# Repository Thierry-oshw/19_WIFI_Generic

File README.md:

# 19_WIFI_Generic
 WIFI board for generic purposes

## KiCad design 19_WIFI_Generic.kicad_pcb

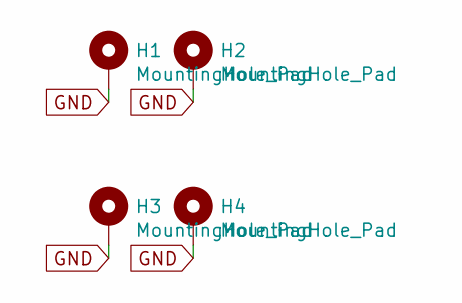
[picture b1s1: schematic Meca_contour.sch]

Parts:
H1, H2, H3, H4: MountingHole_Pad; MountingHole_3.2mm_M3_Pad_Via

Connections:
GND: H1.1, H2.1, H3.1, H4.1; also elsewhere on the board

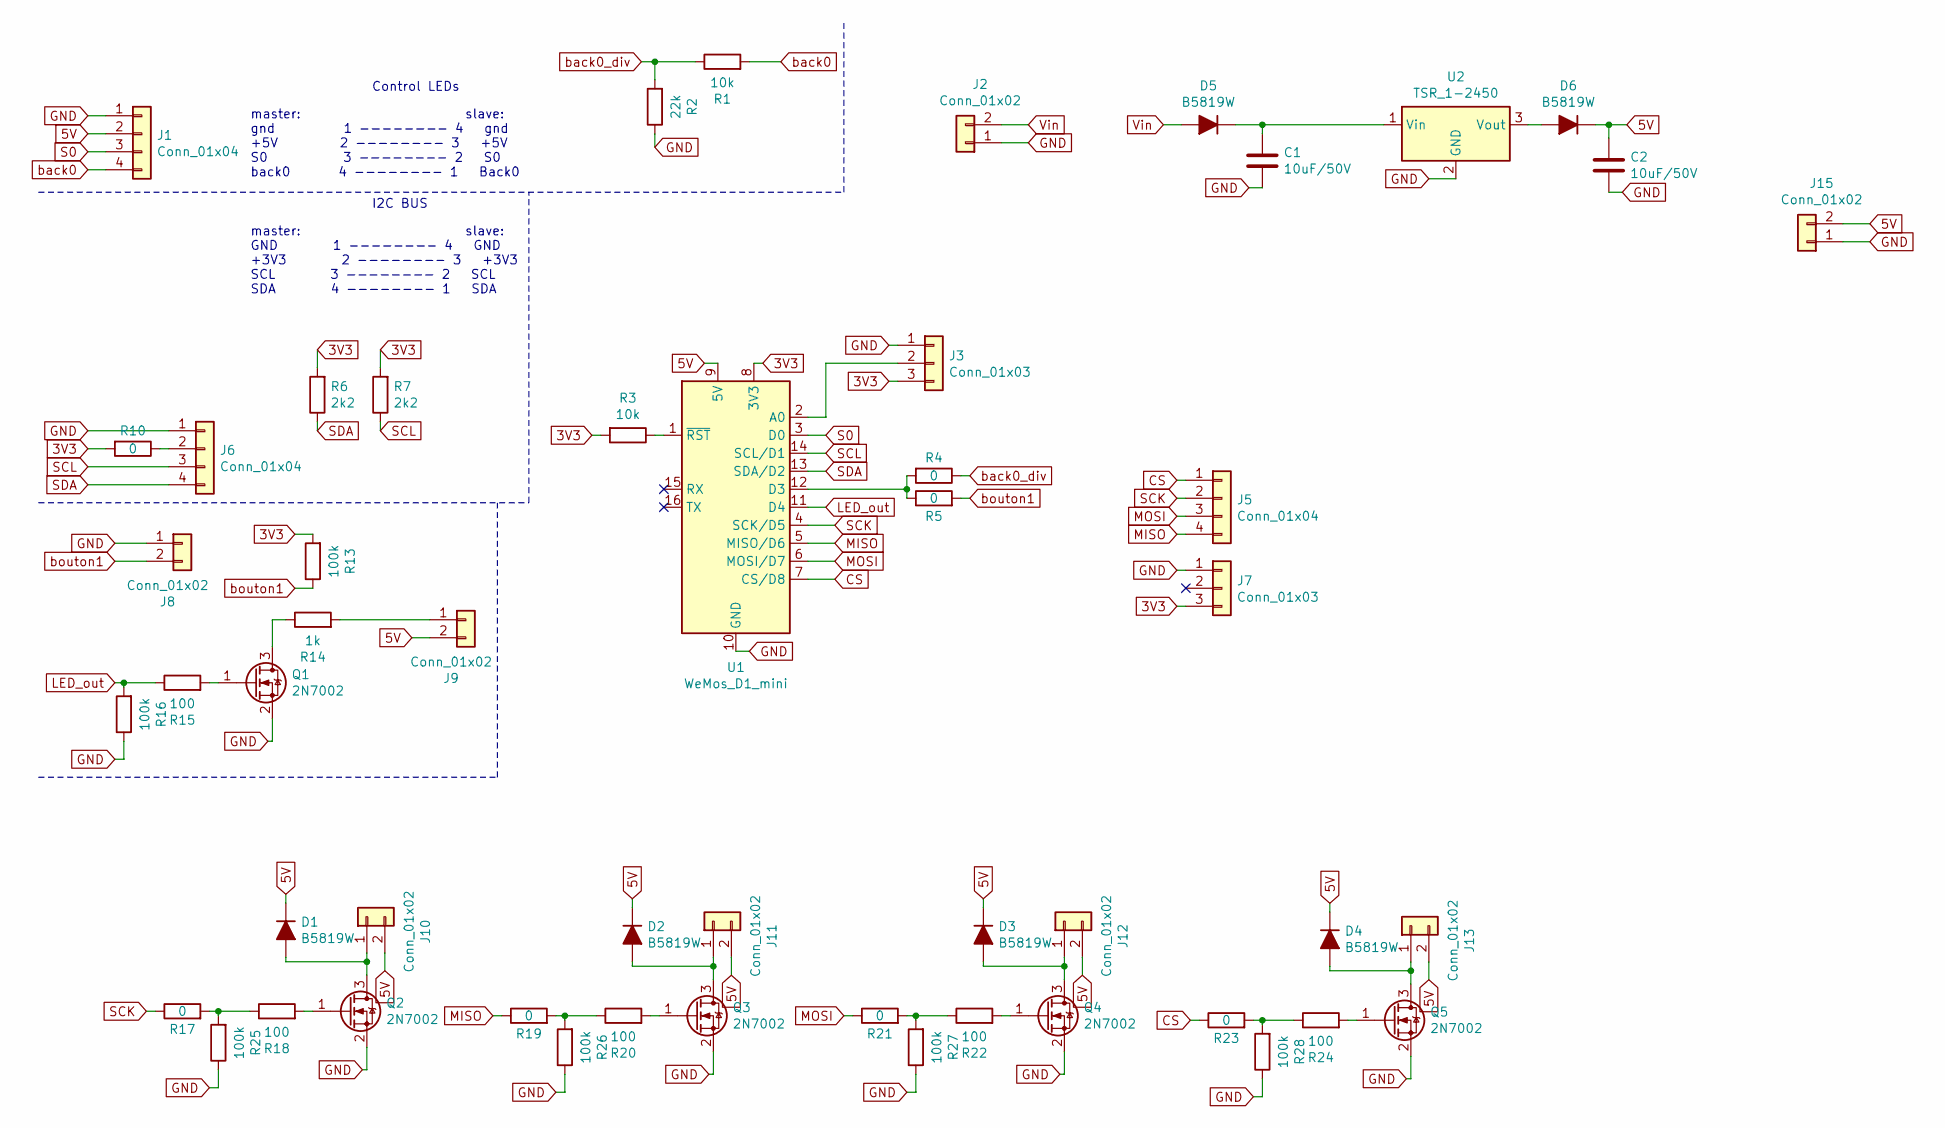
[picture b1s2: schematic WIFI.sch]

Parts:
C1, C2: 10uF/50V; C_1210_3225Metric
D1, D2, D3, D4, D5, D6: B5819W; D_SOD-123
J1, J5, J6: Conn_01x04; JST_XH_B4B-XH-A_1x04_P2.50mm_Vertical
J2, J8, J9, J10, J11, J12, J13, J15: Conn_01x02; JST_XH_B2B-XH-A_1x02_P2.50mm_Vertical
J3, J7: Conn_01x03; JST_XH_B3B-XH-A_1x03_P2.50mm_Vertical
Q1, Q2, Q3, Q4, Q5: 2N7002; SOT-23
R1, R3: 10k; R_0603_1608Metric_Pad1.05x0.95mm_HandSolder
R2: 22k; R_0603_1608Metric_Pad1.05x0.95mm_HandSolder
R4, R5, R10, R17, R19, R21, R23: 0; R_0603_1608Metric_Pad1.05x0.95mm_HandSolder
R6, R7: 2k2; R_0603_1608Metric_Pad1.05x0.95mm_HandSolder
R13, R16, R25, R26, R27, R28: 100k; R_0603_1608Metric_Pad1.05x0.95mm_HandSolder
R14: 1k; R_0603_1608Metric_Pad1.05x0.95mm_HandSolder
R15, R18, R20, R22, R24: 100; R_0603_1608Metric_Pad1.05x0.95mm_HandSolder
U1: WeMos_D1_mini; WEMOS_D1_mini_light
U2: TSR_1-2450; Converter_DCDC_TRACO_TSR-1_THT

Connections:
3V3: J3.3, J7.3, R3.2, R6.2, R7.2, R10.2, R13.2, U1.8 (3V3)
5V: C2.1, D1.1 (K), D2.1 (K), D3.1 (K), D4.1 (K), D6.1 (K), J1.2, J9.2, J10.2, J11.2, J12.2, J13.2, J15.2, U1.9 (5V)
CS: J5.1, R23.1, U1.7 (CS/D8)
GND: C1.2, C2.2, J1.1, J2.1, J3.1, J6.1, J7.1, J8.1, J15.1, Q1.2 (S), Q2.2 (S), Q3.2 (S), Q4.2 (S), Q5.2 (S), R2.1, R16.1, R25.1, R26.1, R27.1, R28.1, U1.10 (GND), U2.2 (GND); also elsewhere on the board
LED_out: R15.1, R16.2, U1.11 (D4)
MISO: J5.4, R19.1, U1.5 (MISO/D6)
MOSI: J5.3, R21.1, U1.6 (MOSI/D7)
unnamed: C1.1, D5.1 (K), U2.1 (Vin)
unnamed: D1.2 (A), J10.1, Q2.3 (D)
unnamed: D2.2 (A), J11.1, Q3.3 (D)
unnamed: D3.2 (A), J12.1, Q4.3 (D)
unnamed: D4.2 (A), J13.1, Q5.3 (D)
unnamed: D6.2 (A), U2.3 (Vout)
unnamed: J3.2, U1.2 (A0)
unnamed: J6.2, R10.1
unnamed: J9.1, R14.2
unnamed: Q1.1 (G), R15.2
unnamed: Q1.3 (D), R14.1
unnamed: Q2.1 (G), R18.2
unnamed: Q3.1 (G), R20.2
unnamed: Q4.1 (G), R22.2
unnamed: Q5.1 (G), R24.2
unnamed: R3.1, U1.1 (~RST)
unnamed: R4.2, R5.1, U1.12 (D3)
unnamed: R17.2, R18.1, R25.2
unnamed: R19.2, R20.1, R26.2
unnamed: R21.2, R22.1, R27.2
unnamed: R23.2, R24.1, R28.2
S0: J1.3, U1.3 (D0)
SCK: J5.2, R17.1, U1.4 (SCK/D5)
SCL: J6.3, R7.1, U1.14 (SCL/D1)
SDA: J6.4, R6.1, U1.13 (SDA/D2)
Vin: D5.2 (A), J2.2
back0: J1.4, R1.2
back0_div: R1.1, R2.2, R4.1
bouton1: J8.2, R5.2, R13.1

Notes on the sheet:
Control LEDs
master: slave: gnd 1 -------- 4 gnd +5V 2 -------- 3 +5V S0 3 -------- 2 S0 back0 4 -------- 1 Back0
I2C BUS
master: slave: GND 1 -------- 4 GND +3V3 2 -------- 3 +3V3 SCL 3 -------- 2 SCL SDA 4 -------- 1 SDA

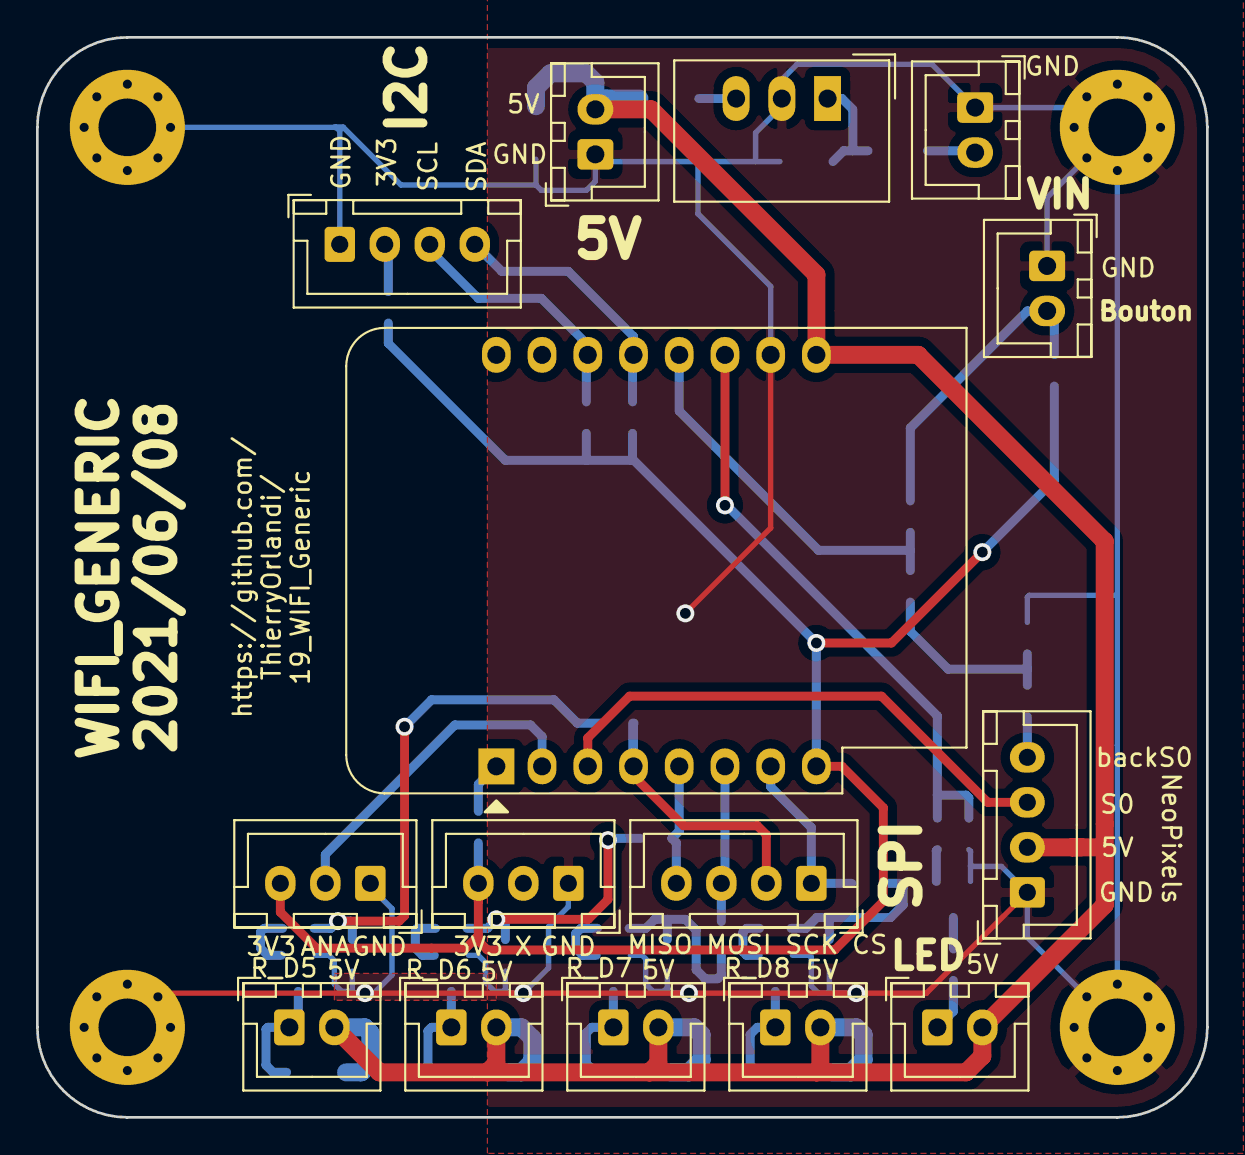
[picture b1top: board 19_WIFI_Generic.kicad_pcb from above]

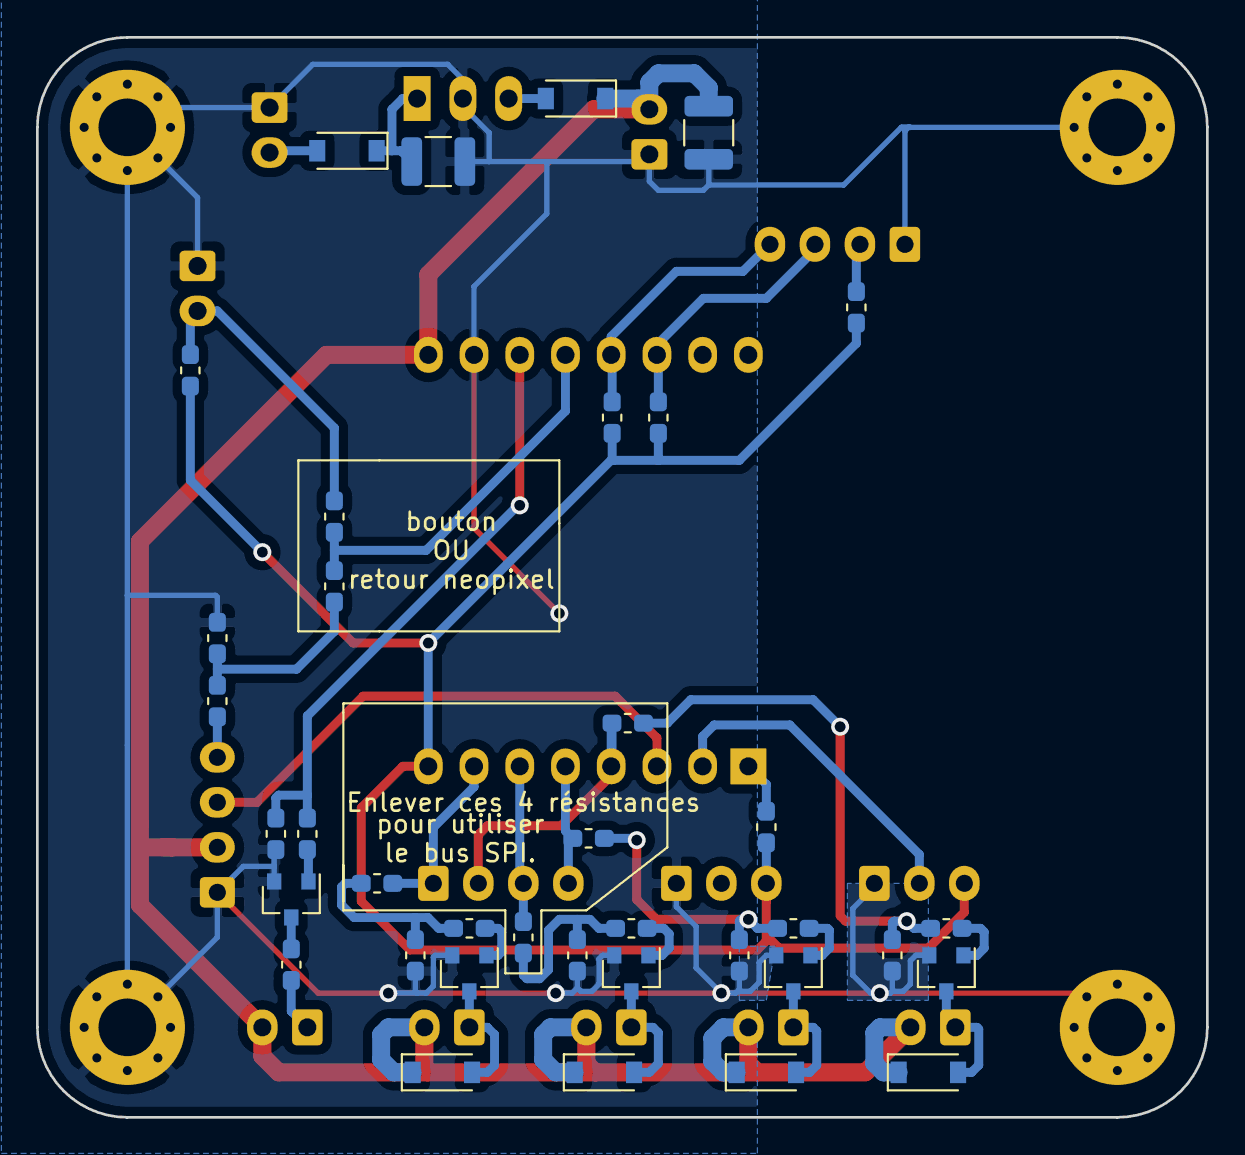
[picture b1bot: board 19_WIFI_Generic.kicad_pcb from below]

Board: 2 copper layers, 65.0 x 60.0 mm, 56 parts (37 on the bottom side), 36 nets.

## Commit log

2021-06-08 schéma + routage
2021-06-08 check
2021-06-10 ajout licence cern
2021-06-11 correction numéro de commande jlcpcb
2021-07-26 maj split librairies
2023-05-02 chgt nom fichier licence
